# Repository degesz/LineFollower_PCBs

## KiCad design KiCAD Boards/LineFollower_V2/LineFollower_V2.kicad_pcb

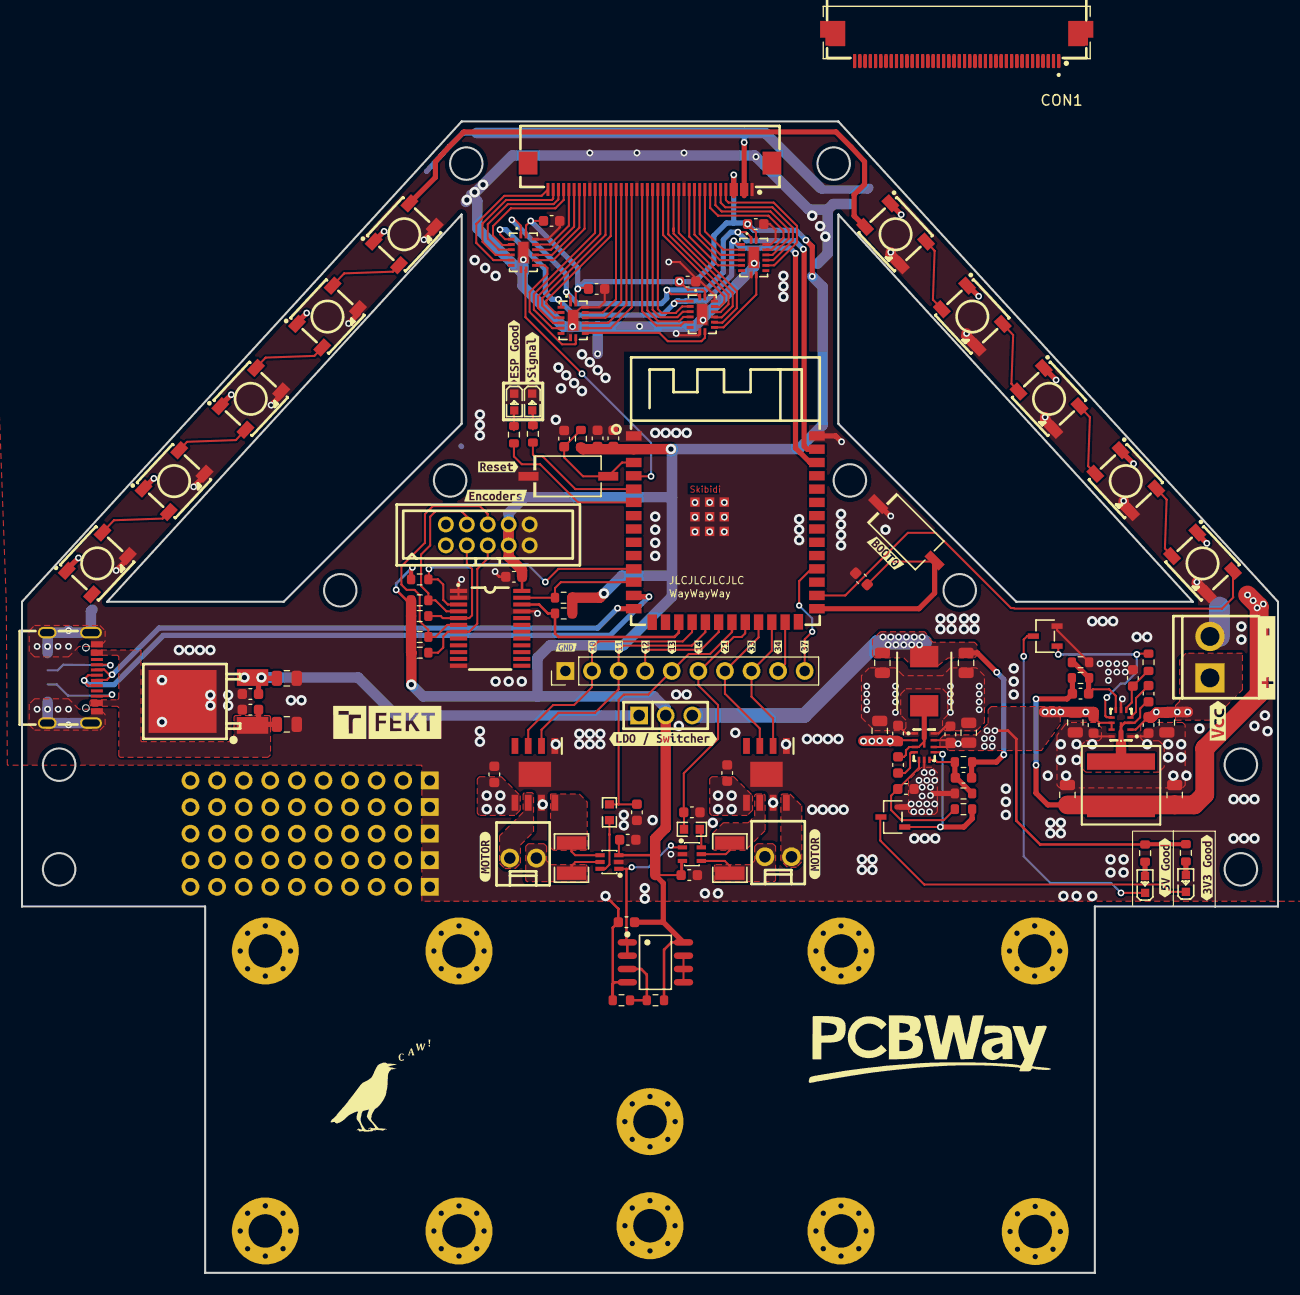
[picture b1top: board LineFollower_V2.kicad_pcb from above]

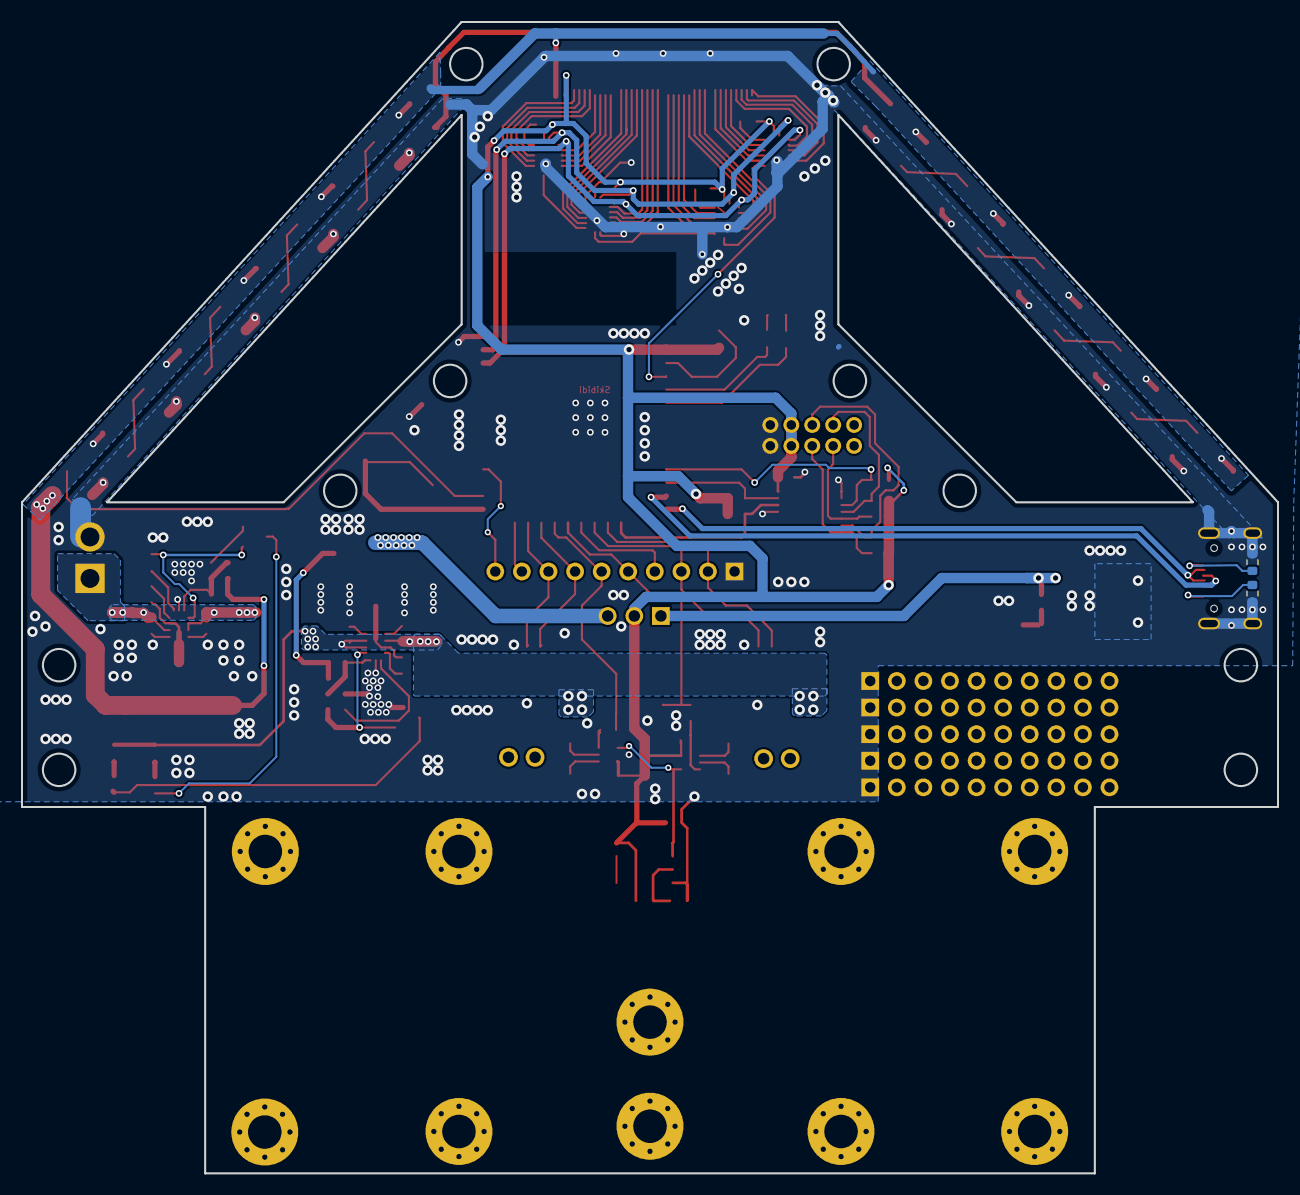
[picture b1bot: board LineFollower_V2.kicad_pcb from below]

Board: 2 copper layers, 120.0 x 110.0 mm, 130 parts (2 on the bottom side), 106 nets.

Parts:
C1, C3, C12, C15, C18, C20, C23, C24, C25, C26: 22uF; C_0805_2012Metric
C2, C4, C11, C14, C17, C19, C33, C34, C35, C36: 220nF; C_0603_1608Metric
C5, C6, C9, C10: 1uF; C_0603_1608Metric
C7, C8, C13, C16, C27, C28, C29, C30, C31, C32: 100nF; C_0603_1608Metric
C21, C22: 20pF; C_0603_1608Metric
C37, C38: 100n; C_0603_1608Metric
CN1, CN2: HC-2510-2A; CONN-TH_2P-P2.54_HCTL_HC-2510-2A
CON1, CON1#3: XDFC-0520-40P; FPC-SMD_40P-P0.50_XDFC-0520-40P
CON1#2: XDFC-0520-40P; AMPHENOL_62684-401100ALF
H1: HDR-TH_3P-P2.54-V-M
IC1: LF33CDT-TRY; TO-252-3_L6.6-W6.1-P4.56-LS9.9-TL
IC2: 2.4GHz; WIRELM-SMD_ESP32-S3-WROOM-1
IC3, IC4: LMR36015FBRNXT; VQFN-12_L3.0-W2.0-P0.65-BL_TI_RNX
IC5, IC6, IC7, IC8: 74HC165BQ,115; DHVQFN-16_L3.5-W2.5-P0.50-BL-EP
IC9: PCA9548APWR; TSSOP-24_L7.8-W4.4-P0.65-LS6.4-BL
IC10: LM358; SOP-8_L4.9-W3.9-P1.27-LS6.0-BL
IC11, IC12: INA199A3DCKR; SOT-363_L2.0-W1.3-P0.65-LS2.1-BR
IC13, IC14: DRV8872DDAR; SOIC127P600X170-9N
J1: Conn_01x10_Pin; PinHeader_1x10_P2.54mm_Vertical
L1: 6.8uH; INDPM5552X200N
L2: 10uH; XAL7030103MEC
LED1, LED2, LED13, LED14: LED0603-RD_GREEN
LED3, LED4, LED5, LED6, LED7, LED8, LED9, LED10, LED11, LED12: 5050; LED-SMD_4P-L5.0-W5.0-BL_TC5050RGB
Q1, Q2: BC817; SOT-23-3_L2.9-W1.4-P1.91-LS2.6-BR
R1, R2, R13, R14, R15, R16, R17, R18: 5k1; R_0603_1608Metric
R3, R4, R5, R12: 10K; R_0603_1608Metric
R6, R7, R8, R10: 100k; R_0603_1608Metric
R9: 43k2; R_0603_1608Metric
R11: 24k9; R_0603_1608Metric
R19, R20: 10kΩ; R_0603_1608Metric
R21, R22: 0.02Ω-1210; R1210
R23, R24: 1k; R0603
R25, R26: 1K; R_0603_1608Metric
SW1, SW2: TS3625A-HT; SW-SMD_L6.1-W3.7-LS7.9
U1: HC-VH-2A-TW; CONN-TH_2P-P3.96_HC-VH-2A-TW
U2: DIP_2*5PIN_80MIL; IDC-TH_10P-P2.00_C9900022934
USB1: USB4105-GF-A; TYPE-C-SMD_SBC-160S1A-20-S412
kibuzzard-669AC45D: G***; kibuzzard-669AC45D
kibuzzard-669AC481: G***; kibuzzard-669AC481
kibuzzard-669BBA84: G***; kibuzzard-669BBA84
kibuzzard-669E1D82, kibuzzard-669E1D82#2: G***; kibuzzard-669E1D82
kibuzzard-669E1EE7: G***; kibuzzard-669E1EE7
kibuzzard-669E1EEE: G***; kibuzzard-669E1EEE
kibuzzard-669E1EFC: G***; kibuzzard-669E1EFC
kibuzzard-669E1F0E: G***; kibuzzard-669E1F0E
kibuzzard-669E1F1F: G***; kibuzzard-669E1F1F
kibuzzard-669E1F2D: G***; kibuzzard-669E1F2D
kibuzzard-669E1F08: G***; kibuzzard-669E1F08
kibuzzard-669E1F24: G***; kibuzzard-669E1F24
kibuzzard-669E1F34: G***; kibuzzard-669E1F34
kibuzzard-669E1F50: G***; kibuzzard-669E1F50
kibuzzard-669E1FB3: G***; kibuzzard-669E1FB3
kibuzzard-669E23C8: G***; kibuzzard-669E23C8
kibuzzard-669E23CE: G***; kibuzzard-669E23CE
kibuzzard-669E206F: G***; kibuzzard-669E206F
kibuzzard-669E2084: G***; kibuzzard-669E2084
kibuzzard-669E2110: G***; kibuzzard-669E2110
kibuzzard-669E2194: G***; kibuzzard-669E2194

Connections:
3V3: C5.1, C6.1, C27.1, C28.1, C29.1, C30.1, C33.1, C34.1, C35.1, C36.1, CON1#3.4, CON1#3.5, H1.2, IC2.2 (3V3), IC5.16 (VCC), IC6.16 (VCC), IC7.16 (VCC), IC8.16 (VCC), IC9.24 (VCC), IC10.8 (Vcc), IC11.3 (V+), IC12.3 (V+), R3.2, R12.2, R13.2, R14.2, R15.2, R16.2, R17.2, R18.2, R19.2, U2.7, U2.8
3V3_LDO_OUT: C3.1, C4.1, H1.1, IC1.2 (OUTPUT)
3V3_SWITCHING_OUT: C21.1, C23.1, C25.1, H1.3, L1.2, R8.2
+5V: C22.1, C24.1, C26.1, CON1#3.2, CON1#3.3, L2.2, LED3.1 (VDD), LED4.1 (VDD), LED5.1 (VDD), LED6.1 (VDD), LED7.1 (VDD), LED8.1 (VDD), LED9.1 (VDD), LED10.1 (VDD), LED11.1 (VDD), LED12.1 (VDD), R10.2
/Motor driver/IC_13_OUT_1: CN1.2, IC13.6 (OUT1)
/Motor driver/IC_14_OUT: CN2.1, IC14.8 (OUT2)
BOOT_3V3: C13.2, IC3.3 (NC), IC3.12 (SW), L1.1
BOOT_5V: C16.2, IC4.3 (NC), IC4.12 (SW), L2.1
CLK_Shift: IC2.38 (IO2), IC5.2 (CP), IC6.2 (CP), IC7.2 (CP), IC8.2 (CP)
DIR1: CON1#3.6, IC8.11 (D0)
DIR2: CON1#3.7, IC8.12 (D1)
DIR3: CON1#3.8, IC8.13 (D2)
DIR4: CON1#3.9, IC8.14 (D3)
DIR5: CON1#3.10, IC8.3 (D4)
DIR6: CON1#3.11, IC8.4 (D5)
DIR7: CON1#3.12, IC8.5 (D6)
DIR8: CON1#3.13, IC8.6 (D7)
DIR9: CON1#3.15, IC7.11 (D0)
DIR10: CON1#3.16, IC7.12 (D1)
DIR11: CON1#3.17, IC7.13 (D2)
DIR12: CON1#3.18, IC7.14 (D3)
DIR13: CON1#3.19, IC7.3 (D4)
DIR14: CON1#3.20, IC7.4 (D5)
DIR15: CON1#3.21, IC7.5 (D6)
DIR16: CON1#3.22, IC7.6 (D7)
DIR17: CON1#3.24, IC5.11 (D0)
DIR18: CON1#3.25, IC5.12 (D1)
DIR19: CON1#3.26, IC5.13 (D2)
DIR20: CON1#3.27, IC5.14 (D3)
DIR21: CON1#3.28, IC5.3 (D4)
DIR22: CON1#3.29, IC5.4 (D5)
DIR23: CON1#3.30, IC5.5 (D6)
DIR24: CON1#3.31, IC5.6 (D7)
DIR25: CON1#3.33, IC6.11 (D0)
DIR26: CON1#3.34, IC6.12 (D1)
DIR27: CON1#3.35, IC6.13 (D2)
DIR28: CON1#3.36, IC6.14 (D3)
DIR29: CON1#3.37, IC6.3 (D4)
DIR30: CON1#3.38, IC6.4 (D5)
DIR31: CON1#3.39, IC6.5 (D6)
DIR32: CON1#3.40, IC6.6 (D7)
ESP_BOOT0: C7.2, IC2.27 (IO0), SW1.1 (A)
ESP_RST: C8.2, IC2.3 (EN), R3.1, SW2.1 (A)
GND: C1.2, C2.2, C3.2, C4.2, C5.2, C6.2, C7.1, C8.1, C9.2, C10.2, C11.2, C12.2, C14.2, C15.2, C17.1, C18.1, C19.1, C20.1, C23.2, C24.2, C25.2, C26.2, C27.2, C28.2, C29.2, C30.2, C31.1, C32.1, C33.2, C34.2, C35.2, C36.2, C37.1, C38.1, CON1#3.1, CON1#3.14, CON1#3.23, CON1#3.32, IC1.3 (GND), IC2.1 (GND), IC2.40 (GND), IC2.41 (GND), IC3.1 (PGND), IC3.6 (AGND), IC3.11 (PGND), IC4.1 (PGND), IC4.6 (AGND), IC4.11 (PGND), IC5.8 (GND), IC5.15 (CE#), IC5.17 (PAD), IC6.8 (GND), IC6.15 (CE#), IC6.17 (PAD), IC7.8 (GND), IC7.15 (CE#), IC7.17 (PAD), IC8.8 (GND), IC8.15 (CE#), IC8.17 (PAD), IC9.1 (A0), IC9.2 (A1), IC9.12 (GND), IC9.21 (A2), IC10.4 (VEE_/_GND), IC11.2 (GND), IC12.2 (GND), IC13.1 (GND), IC13.7 (ISEN), IC13.9 (EP), IC14.1 (GND), IC14.7 (ISEN), IC14.9 (EP), J1.1, LED3.3 (GND), LED4.3 (GND), LED5.3 (GND), LED6.3 (GND), LED7.3 (GND), LED8.3 (GND), LED9.3 (GND), LED10.3 (GND), LED11.3 (GND), LED12.3 (GND), LED13.1 (C), LED14.1 (C), Q1.2 (E), Q2.2 (E), R1.1, R2.1, R9.1, R11.1, R20.1, SW1.2 (B), SW2.2 (B), U1.2, U2.9, U2.10, USB1.1 (EH), USB1.A1 (GND), USB1.A12 (GND), USB1.B1 (GND), USB1.B12 (GND)
I2C_RST: IC2.11 (IO18), IC9.3 (RESET#), R12.1
IO12: IC2.20 (IO12), J1.4
IO34: IC2.25 (IO34), J1.9
IO37: IC2.30 (IO37), J1.10
I_SENS_1: C31.2, IC2.21 (IO13), J1.5, R23.2
I_SENS_1_IN: IC11.4 (IN+), IC13.8 (OUT2), R22.2
I_SENS_1_OUT: CN1.1, IC11.5 (IN-), R22.1
I_SENS_2: C32.2, IC2.22 (IO14), J1.6, R24.2
I_SENS_2_IN: IC12.5 (IN-), IC14.6 (OUT1), R21.1
I_SENS_2_OUT: CN2.2, IC12.4 (IN+), R21.2
LOAD_Shift: IC2.39 (IO1), IC5.1 (PL#), IC6.1 (PL#), IC7.1 (PL#), IC8.1 (PL#)
L_IN_1: IC2.18 (IO10), IC13.3 (IN1), J1.2
L_IN_2: IC2.19 (IO11), IC13.2 (IN2), J1.3
Led_Sig_1: IC2.5 (IO5), R25.2
Led_Sig_2: IC2.6 (IO6), R26.2
MIDPOINT_REF: IC10.1 (OUTPUT_1), IC10.2 (INPUT1(-)), IC11.1 (REF), IC12.1 (REF)
unnamed: C13.1, IC3.4 (BOOT)
unnamed: C21.2, IC3.7 (FB), R8.1, R9.2
unnamed: C9.1, IC3.5 (VCC), R6.2
unnamed: C16.1, IC4.4 (BOOT)
unnamed: C22.2, IC4.7 (FB), R10.1, R11.2
unnamed: C10.1, IC4.5 (VCC), R7.2
unnamed: IC5.10 (DS), IC7.9 (Q7)
unnamed: IC5.9 (Q7), IC6.10 (DS)
unnamed: IC7.10 (DS), IC8.9 (Q7)
unnamed: IC10.3 (INPUT1(+)), R19.1, R20.2
unnamed: IC10.5 (INPUT2(+), IC10.6 (INPUT2(-)), IC10.7 (OUTPUT2)
unnamed: IC11.6 (OUT), R23.1
unnamed: IC12.6 (OUT), R24.1
unnamed: LED1.2 (A), R4.1
unnamed: LED1.1 (C), Q1.3 (C)
unnamed: LED2.2 (A), R5.1
unnamed: LED2.1 (C), Q2.3 (C)
unnamed: LED3.4 (DIN), LED4.2 (DO)
unnamed: LED4.4 (DIN), LED5.2 (DO)
unnamed: LED5.4 (DIN), LED6.2 (DO)
unnamed: LED6.4 (DIN), LED7.2 (DO)
unnamed: LED7.4 (DIN), LED8.2 (DO)
unnamed: LED8.4 (DIN), LED9.2 (DO)
unnamed: LED10.4 (DIN), LED11.2 (DO)
unnamed: LED9.4 (DIN), LED10.2 (DO)
unnamed: LED11.4 (DIN), LED12.2 (DO)
unnamed: LED13.2 (A), R25.1
unnamed: LED14.2 (A), R26.1
unnamed: R2.2, USB1.A5 (CC1)
unnamed: R1.2, USB1.B5 (CC2)
PG_3V3: IC3.8 (PG), Q1.1 (B), R6.1
PG_5V: IC4.8 (PG), Q2.1 (B), R7.1
RGB_DATA: IC2.28 (IO35), LED12.4 (DIN)
R_IN_1: IC2.23 (IO21), IC14.3 (IN1), J1.7
R_IN_2: IC2.24 (IO33), IC14.2 (IN2), J1.8
SCL: IC2.17 (IO9), IC9.22 (SCL), R13.1
SCL_L: IC9.5 (SC0), R16.1, U2.3
SCL_R: IC9.7 (SC1), R15.1, U2.5
SDA: IC2.12 (IO8), IC9.23 (SDA), R14.1
SDA_L: IC9.4 (SD0), R17.1, U2.4
SDA_R: IC9.6 (SD1), R18.1, U2.6
Shift_DATA: IC2.4 (IO4), IC6.9 (Q7)
USB_D+: IC2.13 (IO19), USB1.A6 (DP1), USB1.B6 (DP2)
USB_D-: IC2.14 (IO20), USB1.A7 (DN1), USB1.B7 (DN2)
USB_VBUS: C1.1, C2.1, IC1.1 (INPUT), USB1.A4 (VBUS), USB1.A9 (VBUS), USB1.B4 (VBUS), USB1.B9 (VBUS)
VCC: C11.1, C12.1, C14.1, C15.1, C17.2, C18.2, C19.2, C20.2, C37.2, C38.2, IC3.2 (VIN), IC3.9 (EN), IC3.10 (VIN), IC4.2 (VIN), IC4.9 (EN), IC4.10 (VIN), IC13.5 (VM), IC14.5 (VM), R4.2, R5.2, U1.1

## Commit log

2024-07-18 ported from EasyEDA
2024-07-18 fix values, layout switchers
2024-07-19 some routing
2024-07-20 more routing
2024-07-21 ZubyMakove
2024-09-04 v2 board 1.0
